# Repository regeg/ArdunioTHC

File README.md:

ArdunioTHC
==========

Arduino-based Torch Height Controller for CNC Plasma torch systems

(see "Status.txt" for current project status.)

***

WARNING: CNC systems are inherently dangerous.  Use of this hardware and software is at your own risk.  I am not an expert at CNC systems, THC's or electrical design.  I'm just an embedded software guy who did the hardware design with help from some experienced EE's.

When working with a THC, you're messing with high voltage.  All of the project information is only for use with the acknowledgement and agreement that no statement of safety or appropriateness is offered for any of the information.  Additionally, you take full responsibility for all uses of this hardware, software and documentation.

***

Background
----------
Having recently built a Computer Numeric Control (CNC) driven Plasma torch cutting table, I wanted to add a torch height controller (THC).  I decided to make my own and open source it.

Both the CNC table build and the THC development couldn't have been done without the significant support I received from the folks on the Everlast Forums.  	www.everlastgenerators.com/forums
These are great forums for support with all things welding and plasma cutting.

I have built this THC specifically to work with the Everlast Power Plasma 50 plasma torch.  This is the unit I have and I've been very happy with it.

There are two very significant aspects that make the Everlast PP50 ideal for this project.  They are:
	- Pilot Arc start
	- full CNC interface

Pilot Arc Start - the PP50 offers a "pilot arc" start, this is in contrast to an HF (High Frequency) start.  The HF start is very noisy and has been reported to cause significant interference with computer systems.

Full CNC Interface - all control signals are available on a connector on the back of the PP50.  They are:
	- Torch On (input, dry contact)
	- Arc Good (output, dry contract)
	- Full torch voltage
	- Divided torch voltage

This hardware design uses the full arc voltage.  I've observed about 2 volts of noise on the torch voltage signal, no matter what you use (full voltage or divided voltage).  By using the full voltage and dividing it myself, the noise is kept to a significantly lower percentage of the signal.

I have not tested the THC with any other brand of plasma torch.  It should be a good starting point to make a THC to work with other torches that provide a CNC interface.

Hardware
--------
There are two versions of the shield.  The first is a shield and will work with an Arduino Mega.  This has been the primary platform.  A newly released version uses the Arduino Micro Pro.

The hardware provides:
	- isolated interface to CNC system
	- interface to Power Plasma 50 CNC interface
	- isolated RS-232 (TTL levels) for interface to THC

--

I will be updating all files as the project progresses.  There will be the following subdirectories:
	- "ArduinoSource", using Eclipse plugin from www.baeyens.it/eclipse/
	- "THC Manaul", a users guide to building and use the THC
	- "HardwareDesign", Eagle schematic and PCB layout files
	- "WindowsSource", C# .Net application used to capture cutting data
	- "Mach Plugin", A Mach3 plugin to allow Mach to control the THC

License
-------
This is copyrighted software that is released under the Creative Commons Attribution-NonCommercial-ShareAlike 3.0 license

The unofficial summary is:

You can use it as it is for non-commercial purposes.  If you modify it, you must make the modifications public and attribute the original source to me.

(If you want to license it for commerical use, please contact me.)

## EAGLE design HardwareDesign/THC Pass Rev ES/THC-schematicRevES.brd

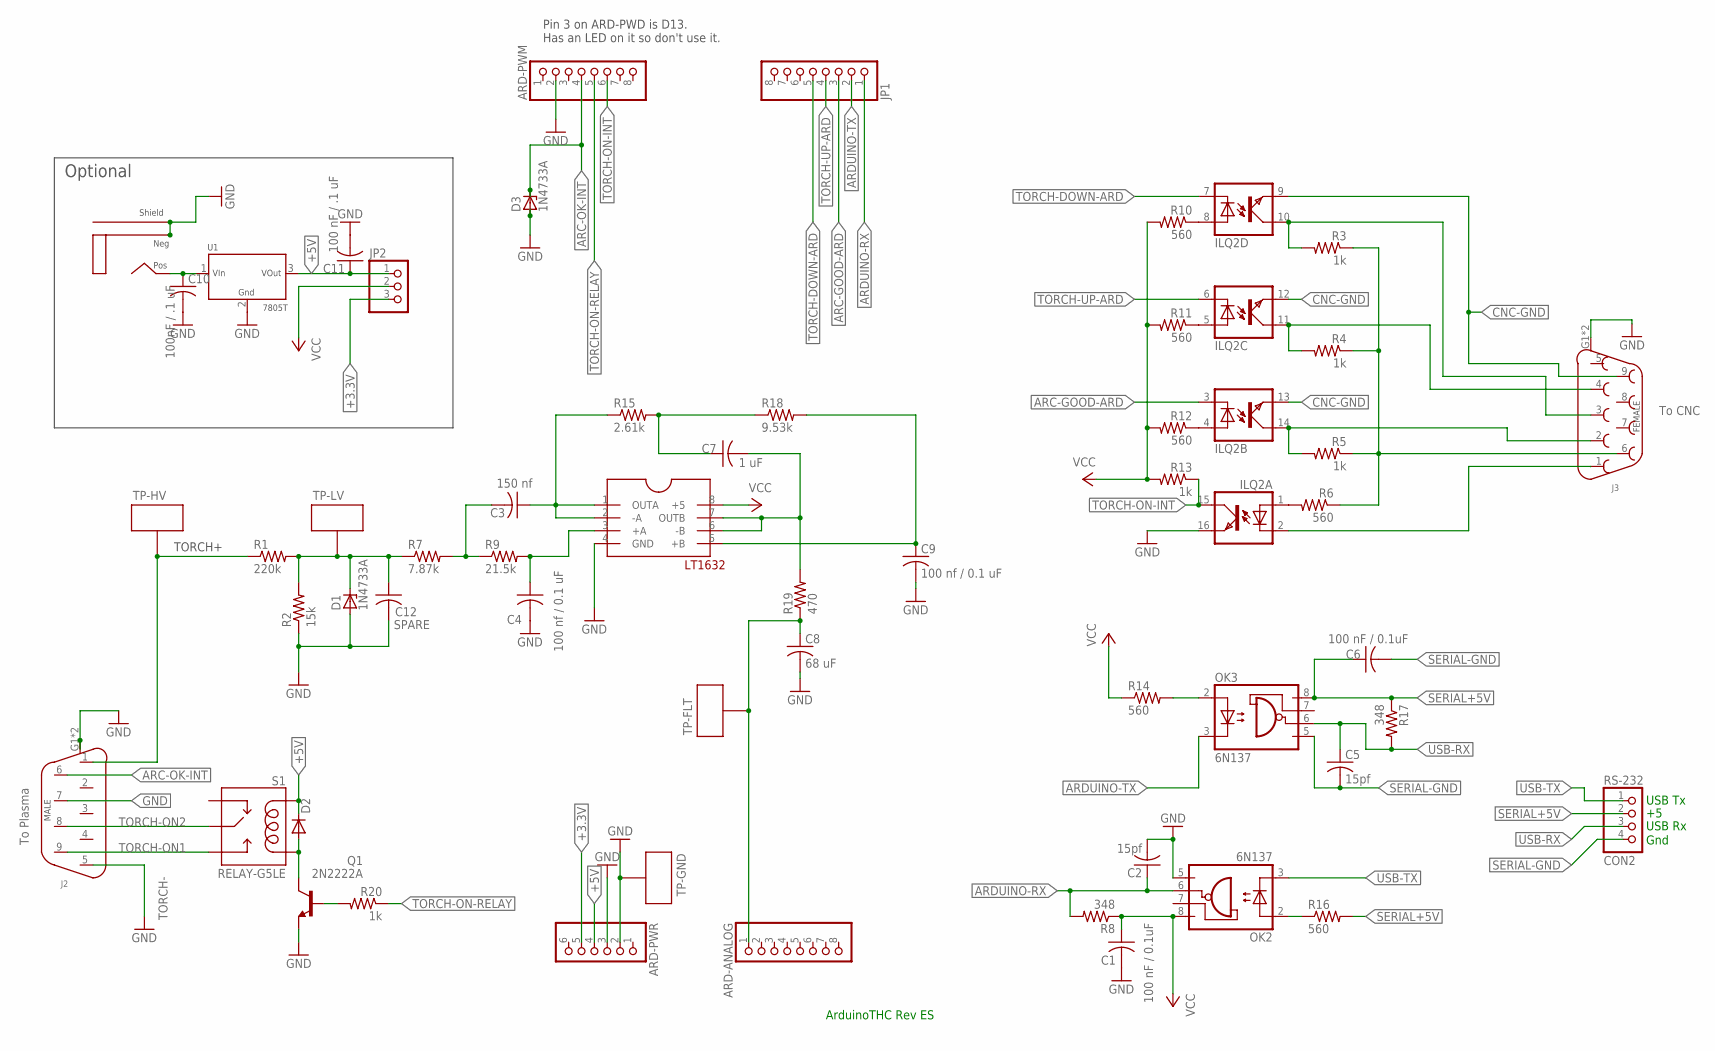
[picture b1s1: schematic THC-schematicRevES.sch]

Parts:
ARD-ANALOG: PINHD-1X8; 1X08
ARD-PWM: PINHD-1X8; 1X08
ARD-PWR: PINHD-1X6; 1X06
C1, C6: 100 nF / 0.1uF; C025-025X050
C2, C5: 15pf; C025-025X050
C3: 150 nf; C025-025X050
C4, C9: 100 nf / 0.1 uF; C025-025X050
C7: 1 uF; C025-025X050
C8: 68 uF; C025-025X050
C10: 100nF / .1 uF; C025-025X050
C11: 100 nF / .1 uF; C025-025X050
C12: SPARE; C025-025X050
D1, D3: 1N4733A; DO41Z10
D2: 1N4001; DO-204AL
ILQ2: ILQ1; DIL16
J1: 2.1MM-PLUG-PCB-MNT; 2.1MM-PLUG
J2: DB9-MALE; DB9M-RIGHT-ANGLE
J3: DB9-FEMALE; DB9F-RIGHT-ANGLE
JP1: PINHD-1X8; 1X08
JP2: PINHD-1X3; 1X03
OK2, OK3: 6N137; DIL08
Q1: 2N2222A; TO18
R1: 220k; 0207/7
R2: 15k; 0207/7
R3, R4, R5, R13, R20: 1k; 0207/7
R6, R10, R11, R12, R14, R16: 560; 0207/7
R7: 7.87k; 0207/7
R8, R17: 348; 0207/7
R9: 21.5k; 0207/7
R15: 2.61k; 0207/7
R18: 9.53k; 0207/7
R19: 470; 0207/7
RS-232: CON2; 1X04
S1: RELAY-G5LE
TP-FLT: TEST-POINT-.040-HOLE; TP.040
TP-GND: TEST-POINT-.040-HOLE; TP.040
TP-HV: TEST-POINT-.040-HOLE; TP.040
TP-LV: TEST-POINT-.040-HOLE; TP.040
U1: 7805T; TO-220-3
U$1: LT1632; DIP08

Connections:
+3.3V: ARD-PWR.5, JP2.3
+5V: ARD-PWR.4, C11.1, D2.C, JP2.1, S1.P$5-COIL (COIL-2), U1.3 (VOUT)
ARC-GOOD-ARD: ILQ2.3 (C), JP1.3
ARC-OK-INT: ARD-PWM.4, D3.C, J2.6
ARD-ANALOG-IN: ARD-ANALOG.1, C8.1, R19.1, TP-FLT.P$1
ARDUINO-RX: C2.1, JP1.1, OK2.6 (VO), R8.2
ARDUINO-TX: JP1.2, OK3.3 (C)
CNC+5: J3.6, R3.1, R4.1, R5.1, R6.1
CNC-ARC-GOOD: ILQ2.14 (COL), J3.2, R5.2
CNC-GND: ILQ2.9 (EMIT), ILQ2.12 (EMIT), ILQ2.13 (EMIT), J3.9
CNC-TORCH-DOWN: ILQ2.10 (COL), J3.3, R3.2
CNC-TORCH-ON: ILQ2.2 (C), J3.1
CNC-TORCH-UP: ILQ2.11 (COL), J3.4, R4.2
DIVIDER: C12.1, D1.C, R1.2, R2.2, R7.1, TP-LV.P$1
GND: ARD-PWM.2, ARD-PWR.2, ARD-PWR.3, C1.2, C2.2, C4.2, C8.2, C9.2, C10.2, C11.2, C12.2, D1.A, D3.A, ILQ2.16 (EMIT), J1.P$NEG, J1.P$SHLD, J2.5, J2.7, J2.G1 (P$SHLD), J2.G2 (P$SHLD), J3.G1 (P$SHLD), J3.G2 (P$SHLD), OK2.5 (GND), Q1.1 (E), R2.1, TP-GND.P$1, U1.2 (GND), U$1.4 (GND)
unnamed: C10.1, J1.P$POS, U1.1 (VIN)
unnamed: ILQ2.4 (A), R12.1
unnamed: D2.A, Q1.3 (C), S1.P$2-COIL (COIL-1)
unnamed: Q1.2 (B), R20.2
unnamed: ILQ2.5 (A), R11.1
unnamed: ILQ2.8 (A), R10.1
unnamed: ILQ2.1 (A), R6.2
unnamed: C3.2, R7.2, R9.1
unnamed: C4.1, R9.2, U$1.3 (+A)
unnamed: C3.1, R15.1, U$1.1 (OUTA), U$1.2 (-A)
unnamed: C7.1, R15.2, R18.1
unnamed: C9.1, R18.2, U$1.5 (+B)
unnamed: OK3.2 (A), R14.2
unnamed: OK2.2 (A), R16.1
SERIAL+5V: C6.1, OK3.8 (VCC), R16.2, R17.1, RS-232.2
SERIAL-GND: C5.2, C6.2, OK3.5 (GND), RS-232.4
TORCH+: J2.1, R1.1, TP-HV.P$1
TORCH-DOWN-ARD: ILQ2.7 (C), JP1.5
TORCH-ON1: J2.9, S1.P$4-NO (NO)
TORCH-ON2: J2.8, S1.P$1-COMMON (COM)
TORCH-ON-INT: ARD-PWM.6, ILQ2.15 (COL), R13.1
TORCH-ON-RELAY: ARD-PWM.5, R20.1
TORCH-UP-ARD: ILQ2.6 (C), JP1.4
UNFILTERED: C7.2, R19.2, U$1.6 (-B), U$1.7 (OUTB)
USB-RX: C5.1, OK3.6 (VO), R17.2, RS-232.3
USB-TX: OK2.3 (C), RS-232.1
VCC: C1.1, JP2.2, OK2.8 (VCC), R8.1, R10.2, R11.2, R12.2, R13.2, R14.1, U$1.8 (+5)

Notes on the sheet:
USB Tx
USB Rx
Gnd
ArduinoTHC Rev ES
To Plasma
To CNC
TORCH-
Pin 3 on ARD-PWD is D13. Has an LED on it so don't use it.
TORCH+
Optional

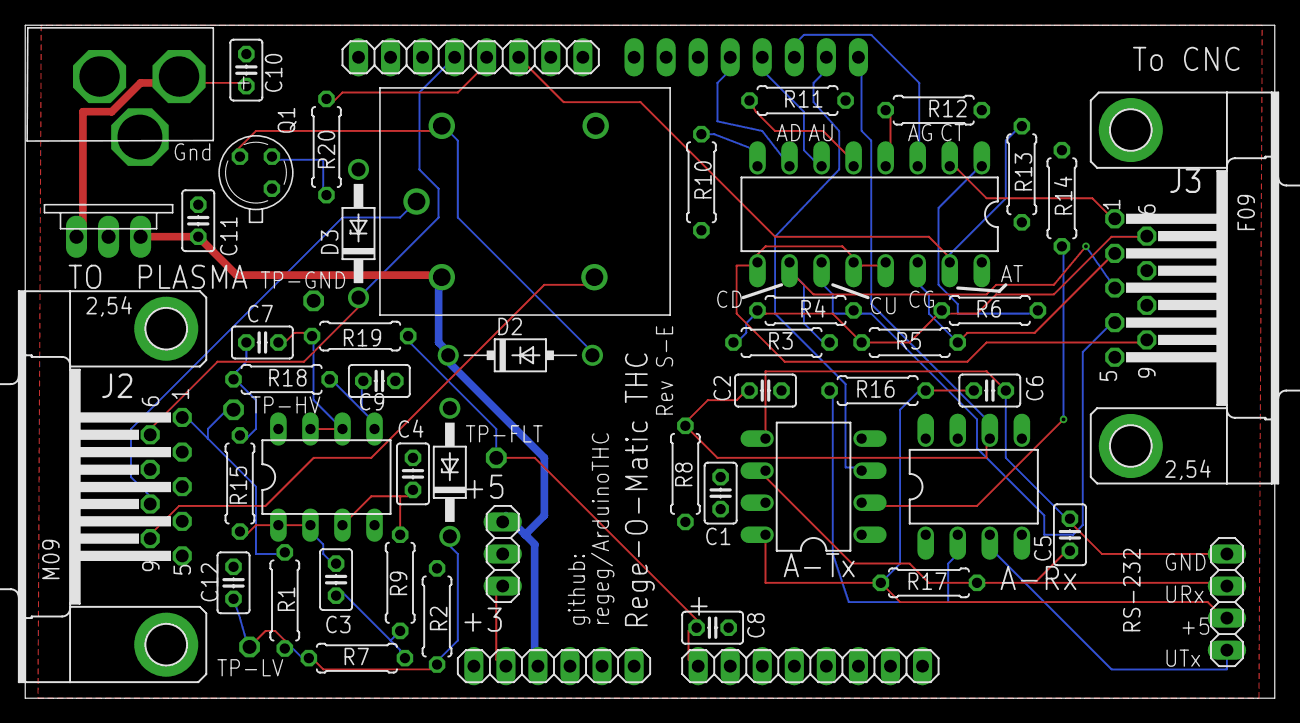
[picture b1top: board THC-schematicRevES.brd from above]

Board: 2 copper layers, 99.0 x 53.3 mm, 55 parts (1 on the bottom side), 42 nets.

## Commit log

2013-01-26 Initial Readme file.
2013-02-10 Rev 0.e - fully functional on modified Rev A board.
2013-02-25 Added significant functionality to serial interface. Changed IO pins for Rev 2.
2013-03-10 Updates for Rev B high speed serial interface.
2013-03-31 .gitignore file added
2013-03-31 Updated .gitignore
2013-04-02 Rev C Hardware
2013-07-15 Updated all files for Rev E-Shield and Rev E-Micro.
2013-07-20 Updated manual to include Micro white wires, BOM, schematics/layouts.
2013-07-20 Added Mach screen w/ bitmaps. Updated Wizard - basic functionality.
2013-07-22 Added section to manual for programming the Arduino. Cleaned up schematic files.
2013-11-23 Fixed issue with kerf detection. Don't know what changed to break it.
2014-01-05 Builds quit working due to illegal file name for sketch. Recreated with existing files under new name. (May have lost some changes.)
2015-02-23 Working files (old updates). I think this is the "fixed" Mach plug-in.
2015-02-24 Release files have the most current DLL build.
2015-06-15 Updated with "PlasmaTHC" custom screen for THC.
